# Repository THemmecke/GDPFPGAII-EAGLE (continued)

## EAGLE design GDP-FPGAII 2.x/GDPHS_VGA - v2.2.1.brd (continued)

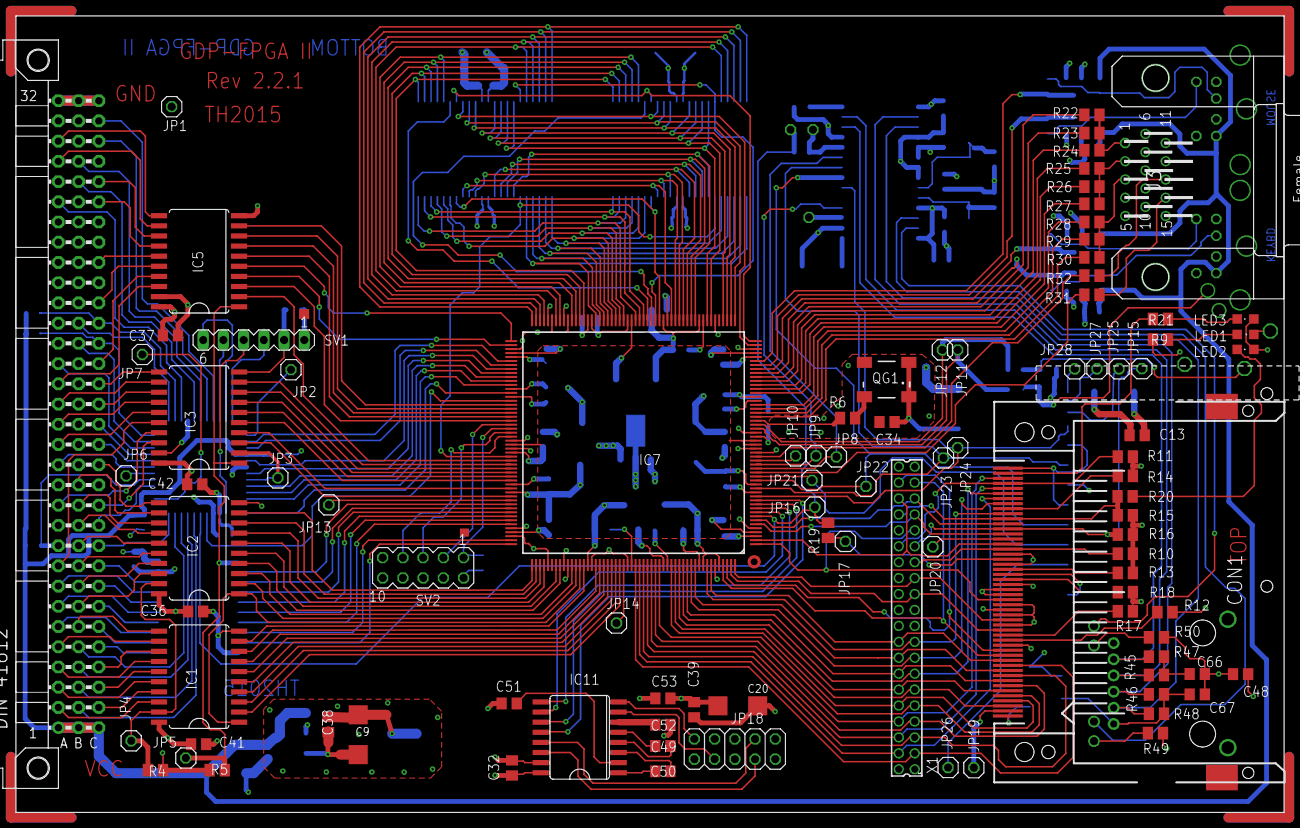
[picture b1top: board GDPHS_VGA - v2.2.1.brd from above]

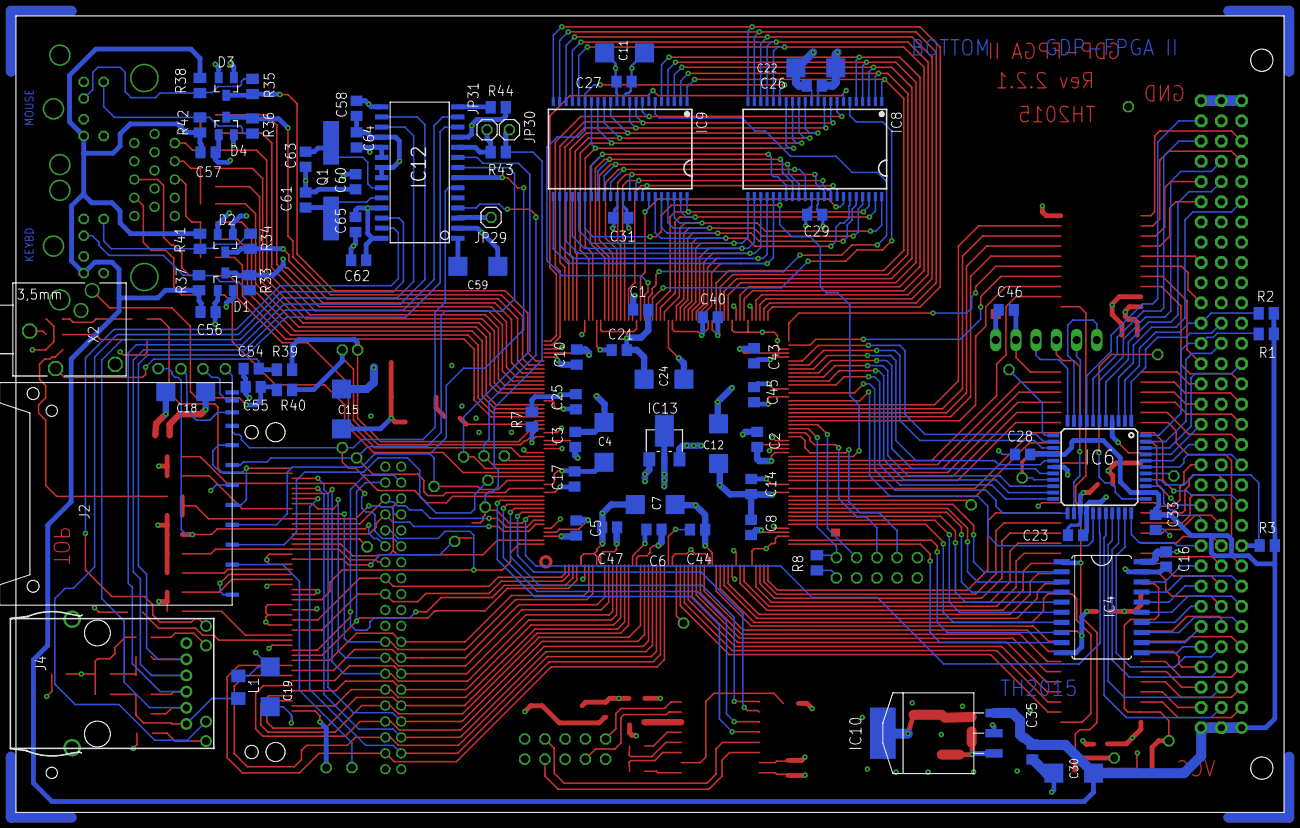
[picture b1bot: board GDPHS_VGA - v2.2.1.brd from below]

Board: 4 copper layers, 159.3 x 100.0 mm, 180 parts (84 on the bottom side), 283 nets.

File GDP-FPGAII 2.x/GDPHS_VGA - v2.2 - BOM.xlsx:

Qty | Value | Device | Package | Parts | Description | MF | MPN | OC_DIGIKEY | OC_FARNELL | OC_REICHELT
1 |  | 08B0-1X1T-36-F08B0-1X1T-36-F | 08B0-1X1T-36-F | J4 |  | Bel Stewart | 08B0-1X1T-36-F | 507-1446-ND
1 |  | L-EUL1206 | L1206 | L1 | INDUCTOR, European symbol | Steward | MI1210K600R-10 | 240-2416-1-ND |  | BLM31PG 500
30 |  | PINHD-1X1 | 1X01 | JP1, JP2, JP3, JP4, JP5, JP6, JP7, JP8, JP9, JP10, JP11, JP12, JP13, JP14, JP15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 | PIN HEADER
5 | 0 | R-EU_M0805 | M0805 | R4, R5, R16, R19, R43 | RESISTOR, European symbol |  |  |  |  | SMD-0805 [10,0K]
50 | 100n | C-EUC0805 | C0805 | C1, C2, C3, C5, C6, C8, C10, C13, C14, C16, C17, C21, C23, C25, C26, C27, C28, 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 | CAPACITOR, European symbol |  |  |  |  | X7R-G0805 [100N]
11 | 10k | R-EU_M0805 | M0805 | R1, R2, R3, R10, R11, R12, R13, R14, R15, R17, R18 | RESISTOR, European symbol |  |  |  |  | SMD-0805 [10,0K]
13 | 10µ/16 | CPOL-EUSMCC | SMC_C | C4, C7, C9, C11, C12, C15, C18, C19, C20, C22, C24, C30, C59 | POLARIZED CAPACITOR, European symbol |  |  |  |  | SMD TAN [10/16]
4 | 120 | R-EU_M0805 | M0805 | R33, R34, R35, R36 | RESISTOR, European symbol |  |  |  |  | SMD-0805 [10,0K]
3 | 1k | R-EU_M0805 | M0805 | R23, R26, R29 | RESISTOR, European symbol |  |  |  |  | SMD-0805 [10,0K]
3 | 1k8 | R-EU_M0805 | M0805 | R24, R27, R30 | RESISTOR, European symbol |  |  |  |  | SMD-0805 [10,0K]
2 | 22p | C-EUC0805 | C0805 | C61, C63 | CAPACITOR, European symbol |  |  |  |  | X7R-G0805 [100N]
5 | 270 | R-EU_M0805 | M0805 | R9, R20, R21, R49, R50 | RESISTOR, European symbol |  |  |  |  | SMD-0805 [10,0K]
4 | 2k | R-EU_M0805 | M0805 | R37, R38, R41, R42 | RESISTOR, European symbol |  |  |  |  | SMD-0805 [10,0K]
1 | 2k7 | R-EU_M0805 | M0805 | R44 | RESISTOR, European symbol |  |  |  |  | SMD-0805 [10,0K]
1 | 330 | R-EU_M0805 | M0805 | R6 | RESISTOR, European symbol |  |  |  |  | SMD-0805 [10,0K]
2 | 3k3 | R-EU_M0805 | M0805 | R39, R40 | RESISTOR, European symbol |  |  |  |  | SMD-0805 [10,0K]
2 | 47 | R-EU_M0805 | M0805 | R31, R32 | RESISTOR, European symbol |  |  |  |  | SMD-0805 [10,0K]
3 | 470 | R-EU_M0805 | M0805 | R22, R25, R28 | RESISTOR, European symbol |  |  |  |  | SMD-0805 [10,0K]
2 | 4k7 | R-EU_M0805 | M0805 | R7, R8 | RESISTOR, European symbol |  |  |  |  | SMD-0805 [10,0K]
2 | 4n7 | C-EUC0805 | C0805 | C54, C55 | CAPACITOR, European symbol |  |  |  |  | X7R-G0805 [100N]
4 | 50 | R-EU_M0805 | M0805 | R45, R46, R47, R48 | RESISTOR, European symbol |  |  |  |  | SMD-0805 [10,0K]
5 | 74LVC245 | 74LVC245DW | SO20W | IC1, IC2, IC3, IC4, IC5 | Octal BUS TRANSCEIVER, 3-state | Texas Instruments | SN74LVC245ADWR | 296-1232-1-ND
1 | 87758-4016 | 87758-4016 | 87758-4016 | X1 | 40 Pin - 2mm Dual Row Single Wafer, Vertical T/H HDR |  | 87758-4016 |  | unknown
4 | BAT54S | DIODE_2CACA-SOT23 | SOT23 | D1, D2, D3, D4 | 2 Diodes - Cathode-Anode|Cathode-Anode |  |  |  |  | BAT 54S SMD
1 | CFPS32 - 40MHz | CRYSTAL_RESONATORCFPS7X | CFPS7X | QG1 | CRYSTAL RESONATOR | IQD FREQUENCY PRODUCTS | LF SPXO018042 - QUARZ, 40MHZ, 15PF, SMD |  | 9713565
1 | CSM-7X-DU 25MHz | CSM-7X-DU | CSM-7X-DU | Q1 | SMD CRYSTAL | CITIZEN | CS10-25.000MABJTR | 300-8105-1-ND | unknown
1 | ECB-BUS | VG96K | VG96K | J1 | PCB EUROCARD, 96-pin type C/ABC, 2.54 mm |  |  |  |  | ML-C 96W
1 | ENC28J60SOIC28W | ENC28J60SOIC28W | SO28W | IC12 | Stand-Alone Ethernet Controller with SPI Interface | MICROCHIP |  | ENC28J60-I/SO-ND |  | ENC 28J60-I/SO
1 | FPS-009-2405-0 | FPS-009-2405-0 | FPS-009-2405-0 | J2 | YAMAI SD Card - FPS Series 009-2405-0 | Yamaichi | FPS-009-2405-0 |  |  | CONNECTOR SD 22
1 | GREEN | LEDCHIPLED_0805 | CHIPLED_0805 | LED1 | LED |  |  |  |  | SMD-LED 1206 [GN|RT|GE]
1 | IDE | CF-CARD-IDE_MODEYAMAI-CF-CARD-I-II | CF-050-P2-X03-10-DS-1 | CON1 | Compact Flash Adapter Type I or II without Eject Button | Yamaichi | CF-050P2-103-10-DS1 |  |  | CONNECTOR CF 02
2 | IS64WV51216TSOP44 | IS64WV51216TSOP44 | TSOP44-400 | IC8, IC9 |  | Cypress | CY7C1051DV33-10ZSXI | 428-3241-ND
1 | LFXP2C_XX208-2 | LFXP2C_XX208-2 | PQFP_208 | IC7 |  | Lattice | LFXP2-8E-5QN208C | 220-1253-ND
1 | LT1086-3.3V | LT1086 | MDD | IC10 |  | Linear Technology | LT1086CM-3.3#PBF | LT1086CM-3.3#PBF-ND
1 | LatticeProg | MA05-2 | MA05-2 | SV2 | PIN HEADER |  |  |  | unknown
1 | MAX232ECWE | MAX232ECWE | SO16L | IC11 | RS232 TRANSCEIVER | MAXIM | MAX232ECWE+ |  | 9724435
1 | MDSSV-BD06-HF15B | MDSSV-BD06-HF15B | MDSSV-BD06-HF15-B | J3 |  | Norcomp Inc. | 999-H15-PS2L571 | 999-H15FA-ND
1 | PG203J | PG203J | PG203J | X2 | MIC/HEADPHONE JACK |  |  |  |  | EBS 35 BL
1 | RED | LEDCHIPLED_0805 | CHIPLED_0805 | LED2 | LED |  |  |  |  | SMD-LED 1206 [GN|RT|GE]
1 | RS232 | PINHD-2X5 | 2X05 | JP18 | PIN HEADER
1 | XC9536SMD | XC9536SMD | TQFP44 | IC6
1 | XilinxProg | MA06-1 | MA06-1 | SV1 | PIN HEADER |  |  |  | unknown
1 | YELLOW | LEDCHIPLED_0805 | CHIPLED_0805 | LED3 | LED |  |  |  |  | SMD-LED 1206 [GN|RT|GE]

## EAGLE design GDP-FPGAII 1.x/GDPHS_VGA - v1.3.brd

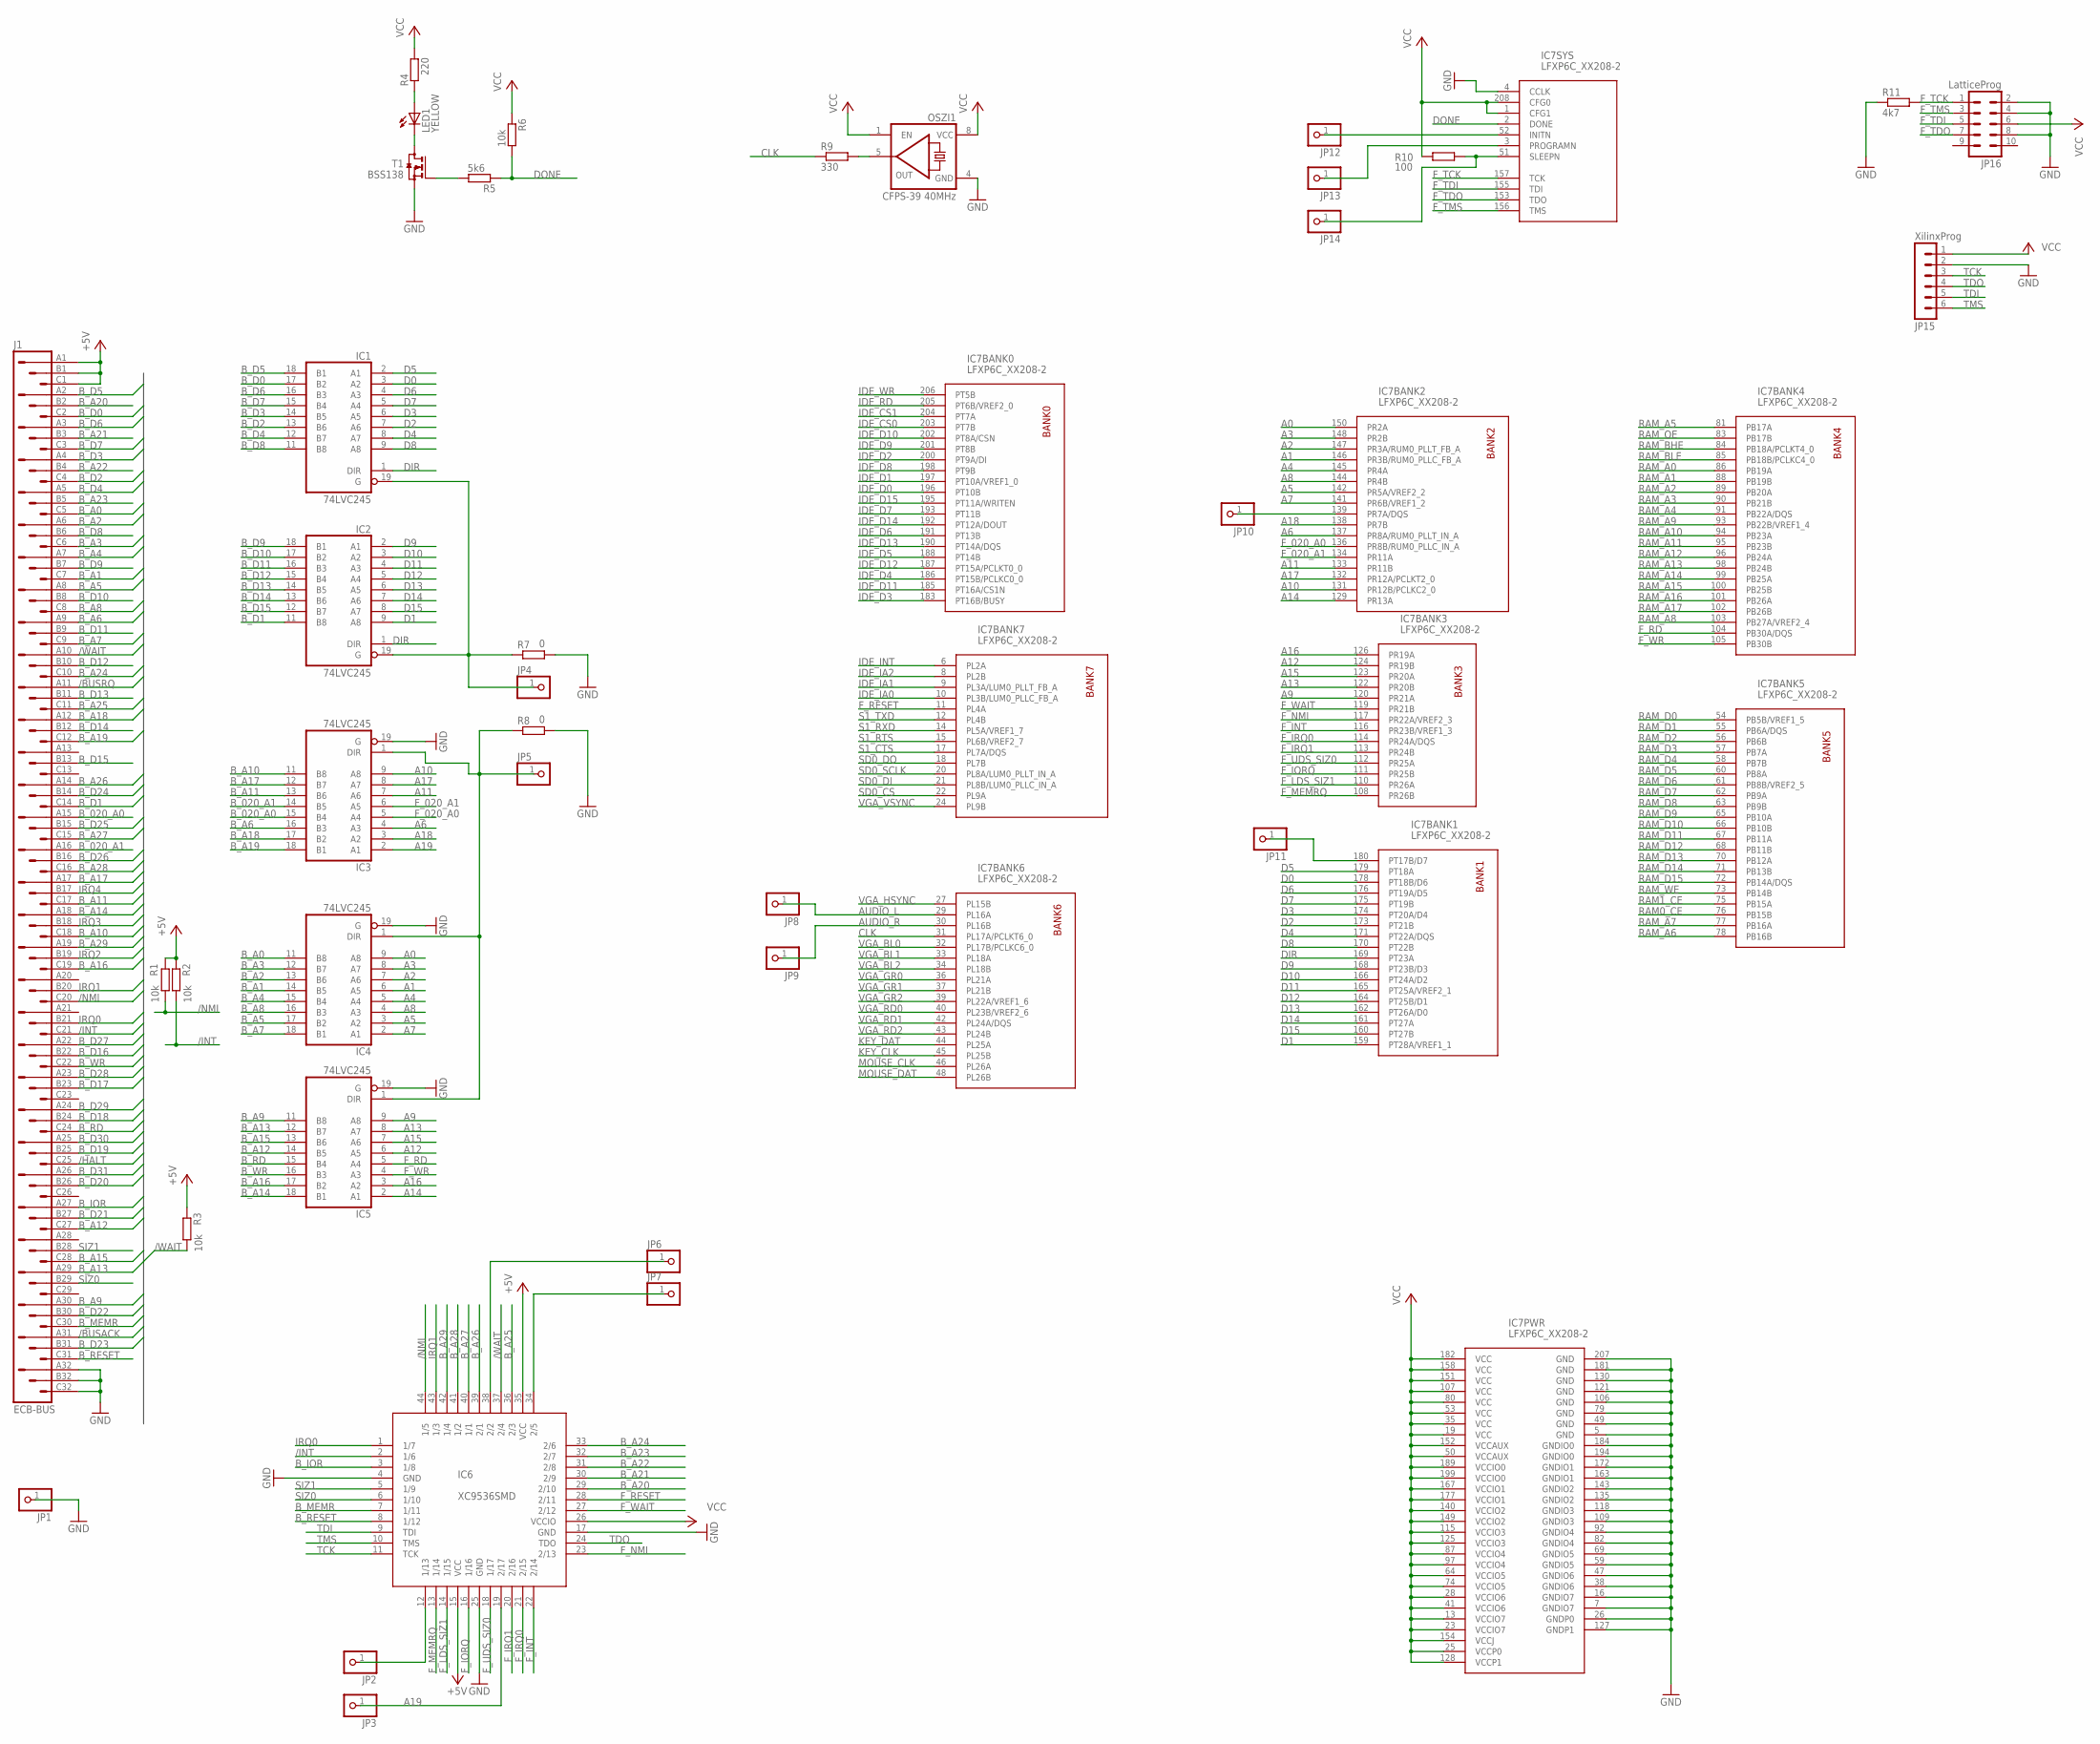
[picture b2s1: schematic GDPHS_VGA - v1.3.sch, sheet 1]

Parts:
IC1, IC2, IC3, IC4, IC5: 74LVC245; SO20W; MPN SN74LVC245ADWR
IC6: XC9536SMD; TQFP44; MPN XC9536-7VQ44C
IC7: LFXP6C_XX208-2; PQFP_208; MPN LFXP6C-3QN208C
J1: ECB-BUS; VG96K
JP1, JP2, JP3, JP4, JP5, JP6, JP7, JP8, JP9, JP10, JP11, JP12, JP13, JP14: PINHD-1X1; 1X01
JP15: XilinxProg; MA06-1
JP16: LatticeProg; MA05-2
LED1: YELLOW; CHIPLED_0805
OSZI1: CFPS-39 40MHz; CFPS7X; MPN LF SPXO018042 - QUARZ, 40MHZ, 15PF, SMD
R1, R2, R3, R6: 10k; M0805
R4: 220; M0805
R5: 5k6; M0805
R7, R8: 0; M0805
R9: 330; M0805
R10: 100; M0805
R11: 4k7; M0805
T1: BSS138; SOT23; MPN BSS138

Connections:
$34: IC6.38 (2/2), JP6.1
+5V: IC6.15 (VCC), IC6.35 (VCC), J1.A1, J1.B1, J1.C1, R1.2, R2.2, R3.2; also elsewhere on the board
/BUSACK: J1.A31
/BUSRQ: J1.A11
/HALT: J1.C25
/INT: IC6.2 (1/6), J1.C21, R2.1
/NMI: IC6.44 (1/5), J1.C20, R1.1
/WAIT: IC6.37 (2/4), J1.A10, R3.1
A0: IC4.9 (A8), IC7.150 (PR2A)
A1: IC4.6 (A5), IC7.146 (PR3B/RUM0_PLLC_FB_A)
A2: IC4.7 (A6), IC7.147 (PR3A/RUM0_PLLT_FB_A)
A3: IC4.8 (A7), IC7.148 (PR2B)
A4: IC4.5 (A4), IC7.145 (PR4A)
A5: IC4.3 (A2), IC7.142 (PR5A/VREF2_2)
A6: IC3.4 (A3), IC7.137 (PR8A/RUM0_PLLT_IN_A)
A7: IC4.2 (A1), IC7.141 (PR6B/VREF1_2)
A8: IC4.4 (A3), IC7.144 (PR4B)
A9: IC5.9 (A8), IC7.120 (PR21A)
A10: IC3.9 (A8), IC7.131 (PR12B/PCLKC2_0)
A11: IC3.7 (A6), IC7.133 (PR11B)
A12: IC5.6 (A5), IC7.124 (PR19B)
A13: IC5.8 (A7), IC7.122 (PR20B)
A14: IC5.2 (A1), IC7.129 (PR13A)
A15: IC5.7 (A6), IC7.123 (PR20A)
A16: IC5.3 (A2), IC7.126 (PR19A)
A17: IC3.8 (A7), IC7.132 (PR12A/PCLKT2_0)
A18: IC3.3 (A2), IC7.138 (PR7B)
A19: IC3.2 (A1), IC6.19 (2/17), JP3.1
AUDIO_L: IC7.29 (PL16A), JP8.1; also elsewhere on the board
AUDIO_R: IC7.30 (PL16B), JP9.1; also elsewhere on the board
B_020_A0: IC3.15 (B4), J1.A15
B_020_A1: IC3.14 (B5), J1.A16
B_A0: IC4.11 (B8), J1.C5
B_A1: IC4.14 (B5), J1.C7
B_A2: IC4.13 (B6), J1.A6
B_A3: IC4.12 (B7), J1.C6
B_A4: IC4.15 (B4), J1.A7
B_A5: IC4.17 (B2), J1.A8
B_A6: IC3.16 (B3), J1.A9
B_A7: IC4.18 (B1), J1.C9
B_A8: IC4.16 (B3), J1.C8
B_A9: IC5.11 (B8), J1.A30
B_A10: IC3.11 (B8), J1.C18
B_A11: IC3.13 (B6), J1.C17
B_A12: IC5.14 (B5), J1.C27
B_A13: IC5.12 (B7), J1.A29
B_A14: IC5.18 (B1), J1.A18
B_A15: IC5.13 (B6), J1.C28
B_A16: IC5.17 (B2), J1.C19
B_A17: IC3.12 (B7), J1.A17
B_A18: IC3.17 (B2), J1.A12
B_A19: IC3.18 (B1), J1.C12
B_A20: IC6.29 (2/10), J1.B2
B_A21: IC6.30 (2/9), J1.B3
B_A22: IC6.31 (2/8), J1.B4
B_A23: IC6.32 (2/7), J1.B5
B_A24: IC6.33 (2/6), J1.C10
B_A25: IC6.36 (2/3), J1.C11
B_A26: IC6.39 (2/1), J1.A14
B_A27: IC6.40 (1/1), J1.C15
B_A28: IC6.41 (1/2), J1.C16
B_A29: IC6.42 (1/4), J1.A19
B_D0: IC1.17 (B2), J1.C2
B_D1: IC2.11 (B8), J1.C14
B_D2: IC1.13 (B6), J1.C4
B_D3: IC1.14 (B5), J1.A4
B_D4: IC1.12 (B7), J1.A5
B_D5: IC1.18 (B1), J1.A2
B_D6: IC1.16 (B3), J1.A3
B_D7: IC1.15 (B4), J1.C3
B_D8: IC1.11 (B8), J1.B6
B_D9: IC2.18 (B1), J1.B7
B_D10: IC2.17 (B2), J1.B8
B_D11: IC2.16 (B3), J1.B9
B_D12: IC2.15 (B4), J1.B10
B_D13: IC2.14 (B5), J1.B11
B_D14: IC2.13 (B6), J1.B12
B_D15: IC2.12 (B7), J1.B13
B_D16: J1.B22
B_D17: J1.B23
B_D18: J1.B24
B_D19: J1.B25
B_D20: J1.B26
B_D21: J1.B27
B_D22: J1.B30
B_D23: J1.B31
B_D24: J1.B14
B_D25: J1.B15
B_D26: J1.B16
B_D27: J1.A22
B_D28: J1.A23
B_D29: J1.A24
B_D30: J1.A25
B_D31: J1.A26
B_IOR: IC6.3 (1/8), J1.A27
B_MEMR: IC6.7 (1/11), J1.C30
B_RD: IC5.15 (B4), J1.C24
B_RESET: IC6.8 (1/12), J1.C31
B_WR: IC5.16 (B3), J1.C22
CLK: IC7.31 (PL17A/PCLKT6_0), R9.1
D0: IC1.3 (A2), IC7.178 (PT18B/D6)
D1: IC2.9 (A8), IC7.159 (PT28A/VREF1_1)
D2: IC1.7 (A6), IC7.173 (PT21B)
D3: IC1.6 (A5), IC7.174 (PT20A/D4)
D4: IC1.8 (A7), IC7.171 (PT22A/DQS)
D5: IC1.2 (A1), IC7.179 (PT18A)
D6: IC1.4 (A3), IC7.176 (PT19A/D5)
D7: IC1.5 (A4), IC7.175 (PT19B)
D8: IC1.9 (A8), IC7.170 (PT22B)
D9: IC2.2 (A1), IC7.168 (PT23B/D3)
D10: IC2.3 (A2), IC7.166 (PT24A/D2)
D11: IC2.4 (A3), IC7.165 (PT25A/VREF2_1)
D12: IC2.5 (A4), IC7.164 (PT25B/D1)
D13: IC2.6 (A5), IC7.162 (PT26A/D0)
D14: IC2.7 (A6), IC7.161 (PT27A)
D15: IC2.8 (A7), IC7.160 (PT27B)
DIR: IC1.1 (DIR), IC2.1 (DIR), IC7.169 (PT23A)
DONE: IC7.2 (DONE), R5.1, R6.2
F_020_A0: IC3.5 (A4), IC7.136 (PR8B/RUM0_PLLC_IN_A)
F_020_A1: IC3.6 (A5), IC7.134 (PR11A)
F_INT: IC6.22 (2/14), IC7.116 (PR23B/VREF1_3)
F_IORQ: IC6.16 (1/16), IC7.111 (PR25B)
F_IRQ0: IC6.21 (2/15), IC7.114 (PR24A/DQS)
F_IRQ1: IC6.20 (2/16), IC7.113 (PR24B)
F_LDS_SIZ1: IC6.14 (1/15), IC7.110 (PR26A)
F_MEMRQ: IC6.13 (1/14), IC7.108 (PR26B)
F_NMI: IC6.23 (2/13), IC7.117 (PR22A/VREF2_3)
F_RD: IC5.5 (A4), IC7.104 (PB30A/DQS)
F_RESET: IC6.28 (2/11), IC7.11 (PL4A); also elsewhere on the board
F_TCK: IC7.157 (TCK), JP16.1, R11.2
F_TDI: IC7.155 (TDI), JP16.5
F_TDO: IC7.153 (TDO), JP16.7
F_TMS: IC7.156 (TMS), JP16.3
F_UDS_SIZ0: IC6.18 (1/17), IC7.112 (PR25A)
F_WAIT: IC6.27 (2/12), IC7.119 (PR21B)
F_WR: IC5.4 (A3), IC7.105 (PB30B)
GND: IC1.10 (GND), IC2.10 (GND), IC3.10 (GND), IC3.19 (G), IC4.10 (GND), IC4.19 (G), IC5.10 (GND), IC5.19 (G), IC6.4 (GND), IC6.17 (GND), IC6.25 (GND), IC7.4 (CCLK), IC7.5 (GND), IC7.7 (GNDIO7), IC7.16 (GNDIO7), IC7.26 (GNDP0), IC7.38 (GNDIO6), IC7.47 (GNDIO6), IC7.49 (GND), IC7.59 (GNDIO5), IC7.69 (GNDIO5), IC7.79 (GND), IC7.82 (GNDIO4), IC7.92 (GNDIO4), IC7.106 (GND), IC7.109 (GNDIO3), IC7.118 (GNDIO3), IC7.121 (GND), IC7.127 (GNDP1), IC7.130 (GND), IC7.135 (GNDIO2), IC7.143 (GNDIO2), IC7.163 (GNDIO1), IC7.172 (GNDIO1), IC7.181 (GND), IC7.184 (GNDIO0), IC7.194 (GNDIO0), IC7.207 (GND), J1.A32, J1.B32, J1.C32, JP1.1, JP15.2, JP16.2, JP16.4, JP16.8, OSZI1.4 (GND), R7.1, R8.1, R11.1, T1.2 (S); also elsewhere on the board
IDE_CS0: IC7.203 (PT7B); also elsewhere on the board
IDE_CS1: IC7.204 (PT7A); also elsewhere on the board
IDE_D0: IC7.196 (PT10B); also elsewhere on the board
IDE_D1: IC7.197 (PT10A/VREF1_0); also elsewhere on the board
IDE_D2: IC7.200 (PT9A/DI); also elsewhere on the board
IDE_D3: IC7.183 (PT16B/BUSY); also elsewhere on the board
IDE_D4: IC7.186 (PT15B/PCLKC0_0); also elsewhere on the board
IDE_D5: IC7.188 (PT14B); also elsewhere on the board
IDE_D6: IC7.191 (PT13B); also elsewhere on the board
IDE_D7: IC7.193 (PT11B); also elsewhere on the board
IDE_D8: IC7.198 (PT9B); also elsewhere on the board
IDE_D9: IC7.201 (PT8B); also elsewhere on the board
IDE_D10: IC7.202 (PT8A/CSN); also elsewhere on the board
IDE_D11: IC7.185 (PT16A/CS1N); also elsewhere on the board
IDE_D12: IC7.187 (PT15A/PCLKT0_0); also elsewhere on the board
IDE_D13: IC7.190 (PT14A/DQS); also elsewhere on the board
IDE_D14: IC7.192 (PT12A/DOUT); also elsewhere on the board
IDE_D15: IC7.195 (PT11A/WRITEN); also elsewhere on the board
IDE_IA0: IC7.10 (PL3B/LUM0_PLLC_FB_A); also elsewhere on the board
IDE_IA1: IC7.9 (PL3A/LUM0_PLLT_FB_A); also elsewhere on the board
IDE_IA2: IC7.8 (PL2B); also elsewhere on the board
IDE_INT: IC7.6 (PL2A); also elsewhere on the board
IDE_RD: IC7.205 (PT6B/VREF2_0); also elsewhere on the board
IDE_WR: IC7.206 (PT5B); also elsewhere on the board
IRQ0: IC6.1 (1/7), J1.B21
IRQ1: IC6.43 (1/3), J1.B20
IRQ2: J1.B19
IRQ3: J1.B18
IRQ4: J1.B17
KEY_CLK: IC7.45 (PL25B); also elsewhere on the board
KEY_DAT: IC7.44 (PL25A); also elsewhere on the board
MOUSE_CLK: IC7.46 (PL26A); also elsewhere on the board
MOUSE_DAT: IC7.48 (PL26B); also elsewhere on the board
unnamed: OSZI1.5 (OUT), R9.2
unnamed: LED1.A, R4.1
unnamed: IC7.51 (SLEEPN), JP14.1, R10.2
unnamed: R5.2, T1.1 (G)
unnamed: LED1.C, T1.3 (D)
unnamed: IC7.139 (PR7A/DQS), JP10.1
unnamed: IC6.34 (2/5), JP7.1
unnamed: IC6.12 (1/13), JP2.1
unnamed: IC7.52 (INITN), JP12.1
unnamed: IC7.3 (PROGRAMN), JP13.1
unnamed: IC3.1 (DIR), IC4.1 (DIR), IC5.1 (DIR), JP5.1, R8.2
unnamed: IC1.19 (G), IC2.19 (G), JP4.1, R7.2
unnamed: IC7.180 (PT17B/D7), JP11.1
RAM0_CE: IC7.76 (PB15B); also elsewhere on the board
RAM1_CE: IC7.75 (PB15A); also elsewhere on the board
RAM_A0: IC7.86 (PB19A); also elsewhere on the board
RAM_A1: IC7.88 (PB19B); also elsewhere on the board
RAM_A2: IC7.89 (PB20A); also elsewhere on the board
RAM_A3: IC7.90 (PB21B); also elsewhere on the board
RAM_A4: IC7.91 (PB22A/DQS); also elsewhere on the board
RAM_A5: IC7.81 (PB17A); also elsewhere on the board
RAM_A6: IC7.78 (PB16B); also elsewhere on the board
RAM_A7: IC7.77 (PB16A); also elsewhere on the board
RAM_A8: IC7.103 (PB27A/VREF2_4); also elsewhere on the board
RAM_A9: IC7.93 (PB22B/VREF1_4); also elsewhere on the board
RAM_A10: IC7.94 (PB23A); also elsewhere on the board
RAM_A11: IC7.95 (PB23B); also elsewhere on the board
RAM_A12: IC7.96 (PB24A); also elsewhere on the board
RAM_A13: IC7.98 (PB24B); also elsewhere on the board
RAM_A14: IC7.99 (PB25A); also elsewhere on the board
RAM_A15: IC7.100 (PB25B); also elsewhere on the board
RAM_A16: IC7.101 (PB26A); also elsewhere on the board
RAM_A17: IC7.102 (PB26B); also elsewhere on the board
RAM_BHE: IC7.84 (PB18A/PCLKT4_0); also elsewhere on the board
RAM_BLE: IC7.85 (PB18B/PCLKC4_0); also elsewhere on the board
RAM_D0: IC7.54 (PB5B/VREF1_5); also elsewhere on the board
RAM_D1: IC7.55 (PB6A/DQS); also elsewhere on the board
RAM_D2: IC7.56 (PB6B); also elsewhere on the board
RAM_D3: IC7.57 (PB7A); also elsewhere on the board
RAM_D4: IC7.58 (PB7B); also elsewhere on the board
RAM_D5: IC7.60 (PB8A); also elsewhere on the board
RAM_D6: IC7.61 (PB8B/VREF2_5); also elsewhere on the board
RAM_D7: IC7.62 (PB9A); also elsewhere on the board
RAM_D8: IC7.63 (PB9B); also elsewhere on the board
RAM_D9: IC7.65 (PB10A); also elsewhere on the board
RAM_D10: IC7.66 (PB10B); also elsewhere on the board
RAM_D11: IC7.67 (PB11A); also elsewhere on the board
RAM_D12: IC7.68 (PB11B); also elsewhere on the board
RAM_D13: IC7.70 (PB12A); also elsewhere on the board
RAM_D14: IC7.71 (PB13B); also elsewhere on the board
RAM_D15: IC7.72 (PB14A/DQS); also elsewhere on the board
RAM_OE: IC7.83 (PB17B); also elsewhere on the board
RAM_WE: IC7.73 (PB14B); also elsewhere on the board
S1_CTS: IC7.17 (PL7A/DQS); also elsewhere on the board
S1_RTS: IC7.15 (PL6B/VREF2_7); also elsewhere on the board
S1_RXD: IC7.14 (PL5A/VREF1_7); also elsewhere on the board
S1_TXD: IC7.12 (PL4B); also elsewhere on the board
SD0_CS: IC7.22 (PL9A); also elsewhere on the board
SD0_DI: IC7.21 (PL8B/LUM0_PLLC_IN_A); also elsewhere on the board
SD0_DO: IC7.18 (PL7B); also elsewhere on the board
SD0_SCLK: IC7.20 (PL8A/LUM0_PLLT_IN_A); also elsewhere on the board
SIZ0: IC6.6 (1/10), J1.B29
SIZ1: IC6.5 (1/9), J1.B28
TCK: IC6.11 (TCK), JP15.3
TDI: IC6.9 (TDI), JP15.5
TDO: IC6.24 (TDO), JP15.4
TMS: IC6.10 (TMS), JP15.6
VCC: IC1.20 (VCC), IC2.20 (VCC), IC3.20 (VCC), IC4.20 (VCC), IC5.20 (VCC), IC6.26 (VCCIO), IC7.1 (CFG1), IC7.13 (VCCIO7), IC7.19 (VCC), IC7.23 (VCCIO7), IC7.25 (VCCP0), IC7.28 (VCCIO6), IC7.35 (VCC), IC7.41 (VCCIO6), IC7.50 (VCCAUX), IC7.53 (VCC), IC7.64 (VCCIO5), IC7.74 (VCCIO5), IC7.80 (VCC), IC7.87 (VCCIO4), IC7.97 (VCCIO4), IC7.107 (VCC), IC7.115 (VCCIO3), IC7.125 (VCCIO3), IC7.128 (VCCP1), IC7.140 (VCCIO2), IC7.149 (VCCIO2), IC7.151 (VCC), IC7.152 (VCCAUX), IC7.154 (VCCJ), IC7.158 (VCC), IC7.167 (VCCIO1), IC7.177 (VCCIO1), IC7.182 (VCC), IC7.189 (VCCIO0), IC7.199 (VCCIO0), IC7.208 (CFG0), JP15.1, JP16.6, OSZI1.1 (EN), OSZI1.8 (VCC), R4.2, R6.1, R10.1; also elsewhere on the board
VGA_BL0: IC7.32 (PL17B/PCLKC6_0); also elsewhere on the board
VGA_BL1: IC7.33 (PL18A); also elsewhere on the board
VGA_BL2: IC7.34 (PL18B); also elsewhere on the board
VGA_GR0: IC7.36 (PL21A); also elsewhere on the board
VGA_GR1: IC7.37 (PL21B); also elsewhere on the board
VGA_GR2: IC7.39 (PL22A/VREF1_6); also elsewhere on the board
VGA_HSYNC: IC7.27 (PL15B); also elsewhere on the board
VGA_RD0: IC7.40 (PL23B/VREF2_6); also elsewhere on the board
VGA_RD1: IC7.42 (PL24A/DQS); also elsewhere on the board
VGA_RD2: IC7.43 (PL24B); also elsewhere on the board
VGA_VSYNC: IC7.24 (PL9B); also elsewhere on the board

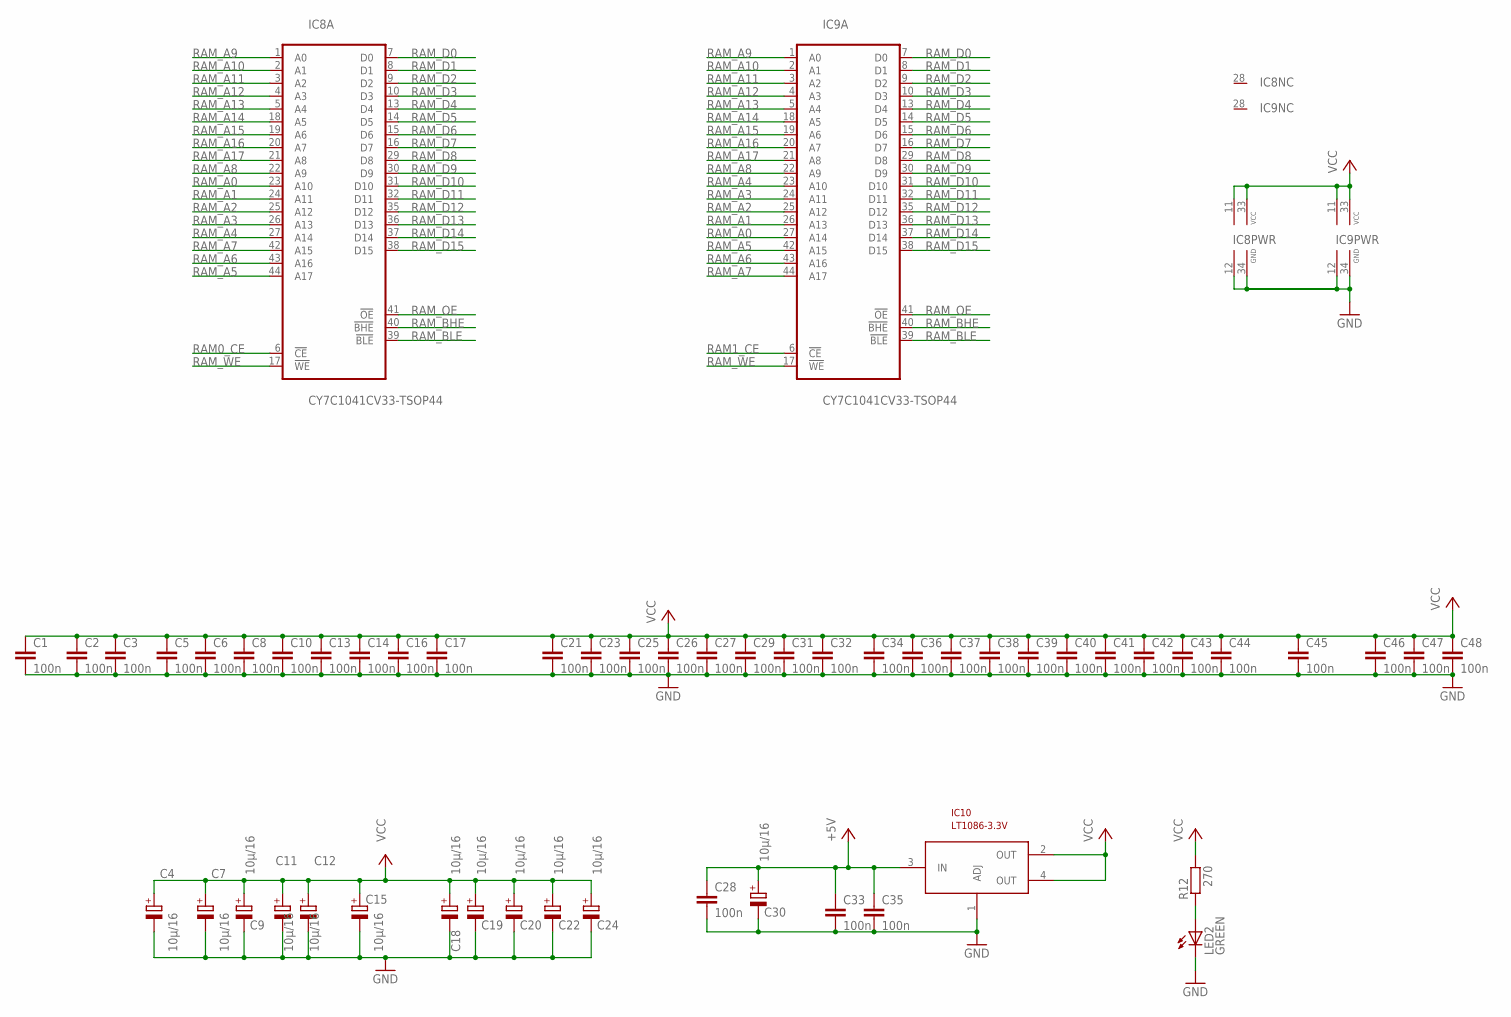
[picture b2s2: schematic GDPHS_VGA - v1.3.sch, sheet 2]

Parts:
C1, C2, C3, C5, C6, C8, C10, C13, C14, C16, C17, C21, C23, C25, C26, C27, C28, C29, C31, C32, C33, C34, C35, C36, C37, C38, C39, C40, C41, C42, C43, C44, C45, C46, C47, C48: 100n; C0805
C4, C7, C9, C11, C12, C15, C18, C19, C20, C22, C24, C30: 10µ/16; SMC_C
IC8, IC9: CY7C1041CV33-TSOP44; TSOP44-400; MPN CY7C1041CV33-10ZSXA
IC10: LT1086-3.3V; MDD; MPN LT1086CM-3.3#PBF
LED2: GREEN; CHIPLED_0805
R12: 270; M0805

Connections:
+5V: C28.1, C30.+, C33.1, C35.1, IC10.3 (IN); also elsewhere on the board
GND: C1.2, C2.2, C3.2, C4.-, C5.2, C6.2, C7.-, C8.2, C9.-, C10.2, C11.-, C12.-, C13.2, C14.2, C15.-, C16.2, C17.2, C18.-, C19.-, C20.-, C21.2, C22.-, C23.2, C24.-, C25.2, C26.2, C27.2, C28.2, C29.2, C30.-, C31.2, C32.2, C33.2, C34.2, C35.2, C36.2, C37.2, C38.2, C39.2, C40.2, C41.2, C42.2, C43.2, C44.2, C45.2, C46.2, C47.2, C48.2, IC8.12 (GND), IC8.34 (GND), IC9.12 (GND), IC9.34 (GND), IC10.1 (ADJ), LED2.C; also elsewhere on the board
unnamed: LED2.A, R12.1
RAM0_CE: IC8.6 (!CE); also elsewhere on the board
RAM1_CE: IC9.6 (!CE); also elsewhere on the board
RAM_A0: IC8.23 (A10), IC9.27 (A14); also elsewhere on the board
RAM_A1: IC8.24 (A11), IC9.26 (A13); also elsewhere on the board
RAM_A2: IC8.25 (A12), IC9.25 (A12); also elsewhere on the board
RAM_A3: IC8.26 (A13), IC9.24 (A11); also elsewhere on the board
RAM_A4: IC8.27 (A14), IC9.23 (A10); also elsewhere on the board
RAM_A5: IC8.44 (A17), IC9.42 (A15); also elsewhere on the board
RAM_A6: IC8.43 (A16), IC9.43 (A16); also elsewhere on the board
RAM_A7: IC8.42 (A15), IC9.44 (A17); also elsewhere on the board
RAM_A8: IC8.22 (A9), IC9.22 (A9); also elsewhere on the board
RAM_A9: IC8.1 (A0), IC9.1 (A0); also elsewhere on the board
RAM_A10: IC8.2 (A1), IC9.2 (A1); also elsewhere on the board
RAM_A11: IC8.3 (A2), IC9.3 (A2); also elsewhere on the board
RAM_A12: IC8.4 (A3), IC9.4 (A3); also elsewhere on the board
RAM_A13: IC8.5 (A4), IC9.5 (A4); also elsewhere on the board
RAM_A14: IC8.18 (A5), IC9.18 (A5); also elsewhere on the board
RAM_A15: IC8.19 (A6), IC9.19 (A6); also elsewhere on the board
RAM_A16: IC8.20 (A7), IC9.20 (A7); also elsewhere on the board
RAM_A17: IC8.21 (A8), IC9.21 (A8); also elsewhere on the board
RAM_BHE: IC8.40 (!BHE), IC9.40 (!BHE); also elsewhere on the board
RAM_BLE: IC8.39 (!BLE), IC9.39 (!BLE); also elsewhere on the board
RAM_D0: IC8.7 (D0), IC9.7 (D0); also elsewhere on the board
RAM_D1: IC8.8 (D1), IC9.8 (D1); also elsewhere on the board
RAM_D2: IC8.9 (D2), IC9.9 (D2); also elsewhere on the board
RAM_D3: IC8.10 (D3), IC9.10 (D3); also elsewhere on the board
RAM_D4: IC8.13 (D4), IC9.13 (D4); also elsewhere on the board
RAM_D5: IC8.14 (D5), IC9.14 (D5); also elsewhere on the board
RAM_D6: IC8.15 (D6), IC9.15 (D6); also elsewhere on the board
RAM_D7: IC8.16 (D7), IC9.16 (D7); also elsewhere on the board
RAM_D8: IC8.29 (D8), IC9.29 (D8); also elsewhere on the board
RAM_D9: IC8.30 (D9), IC9.30 (D9); also elsewhere on the board
RAM_D10: IC8.31 (D10), IC9.31 (D10); also elsewhere on the board
RAM_D11: IC8.32 (D11), IC9.32 (D11); also elsewhere on the board
RAM_D12: IC8.35 (D12), IC9.35 (D12); also elsewhere on the board
RAM_D13: IC8.36 (D13), IC9.36 (D13); also elsewhere on the board
RAM_D14: IC8.37 (D14), IC9.37 (D14); also elsewhere on the board
RAM_D15: IC8.38 (D15), IC9.38 (D15); also elsewhere on the board
RAM_OE: IC8.41 (!OE), IC9.41 (!OE); also elsewhere on the board
RAM_WE: IC8.17 (!WE), IC9.17 (!WE); also elsewhere on the board
VCC: C1.1, C2.1, C3.1, C4.+, C5.1, C6.1, C7.+, C8.1, C9.+, C10.1, C11.+, C12.+, C13.1, C14.1, C15.+, C16.1, C17.1, C18.+, C19.+, C20.+, C21.1, C22.+, C23.1, C24.+, C25.1, C26.1, C27.1, C29.1, C31.1, C32.1, C34.1, C36.1, C37.1, C38.1, C39.1, C40.1, C41.1, C42.1, C43.1, C44.1, C45.1, C46.1, C47.1, C48.1, IC8.11 (VCC), IC8.33 (VCC2), IC9.11 (VCC), IC9.33 (VCC2), IC10.2 (OUT), IC10.4 (OUT), R12.2; also elsewhere on the board
